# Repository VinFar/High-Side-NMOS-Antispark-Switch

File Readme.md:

High Side milliOhm NMOS Anti Spark Switch
===
# Introduction

This PCB is an Anti-Spark switch for high capacitive loads (100A, 60V) and was especially designed for electric longboards.
It uses 10 TPW1R306PL milliOhm N-MOSFET, which have a Rdson of around 90 uOhm in the worst case,
which theoretically enables a maximum current of around 125A with sufficient cooling.

Inspired by the [DieBieMS](https://github.com/DieBieEngineering/DieBieMS) it uses a BQ76200PWR HighSide MOSFET driver,
to enable the high switching with NMOS.

## Features

The PCB includes the following features:
  - dimensions: 74mm x 38.2mm
  - maximum current of at least 125A (more with additional copper and cooling)
  - maximum voltage of 60V
  - controlled dI/dt with capacitor and current limiting resistor
  - 10 TPW1R306PL N-channel MOSFET
  - BQ76200PWR High Side MOSFET Driver
  - A TPS7A4101DGNR 12V 50mA LDO
  - A holder for a LittleFuse BF1
  - 4 pin JST XH connector for external switch or MCU
  - exposed pcb traces to add solder or a copper bar for lower resistance

### Versions
  - V0.1 is the initial version (08.09.19)
  - V0.2 uses 10 TPW1R306PL mosfet instead of two IRFS7530 (09.09.19)

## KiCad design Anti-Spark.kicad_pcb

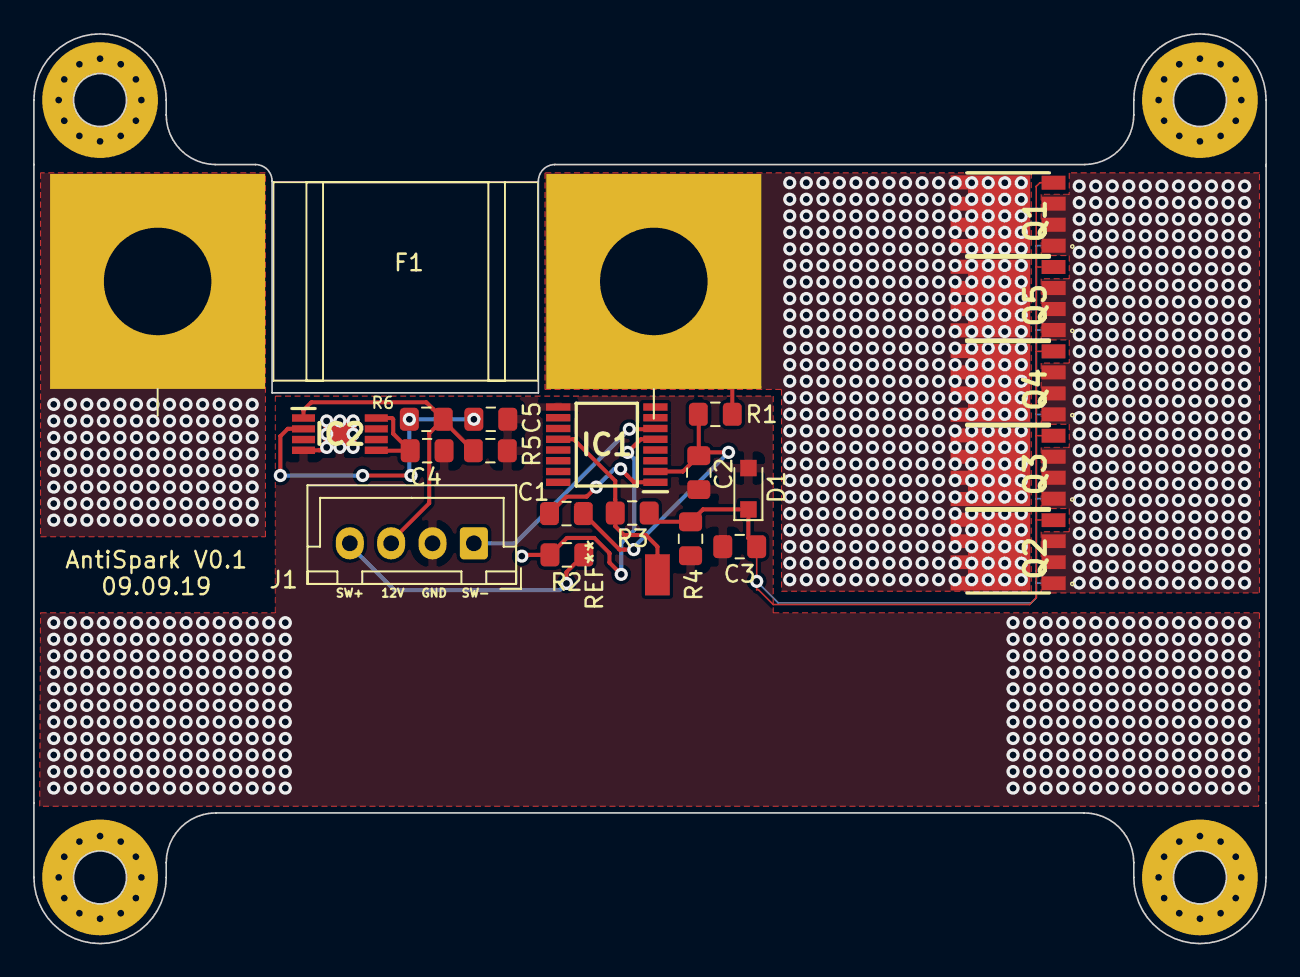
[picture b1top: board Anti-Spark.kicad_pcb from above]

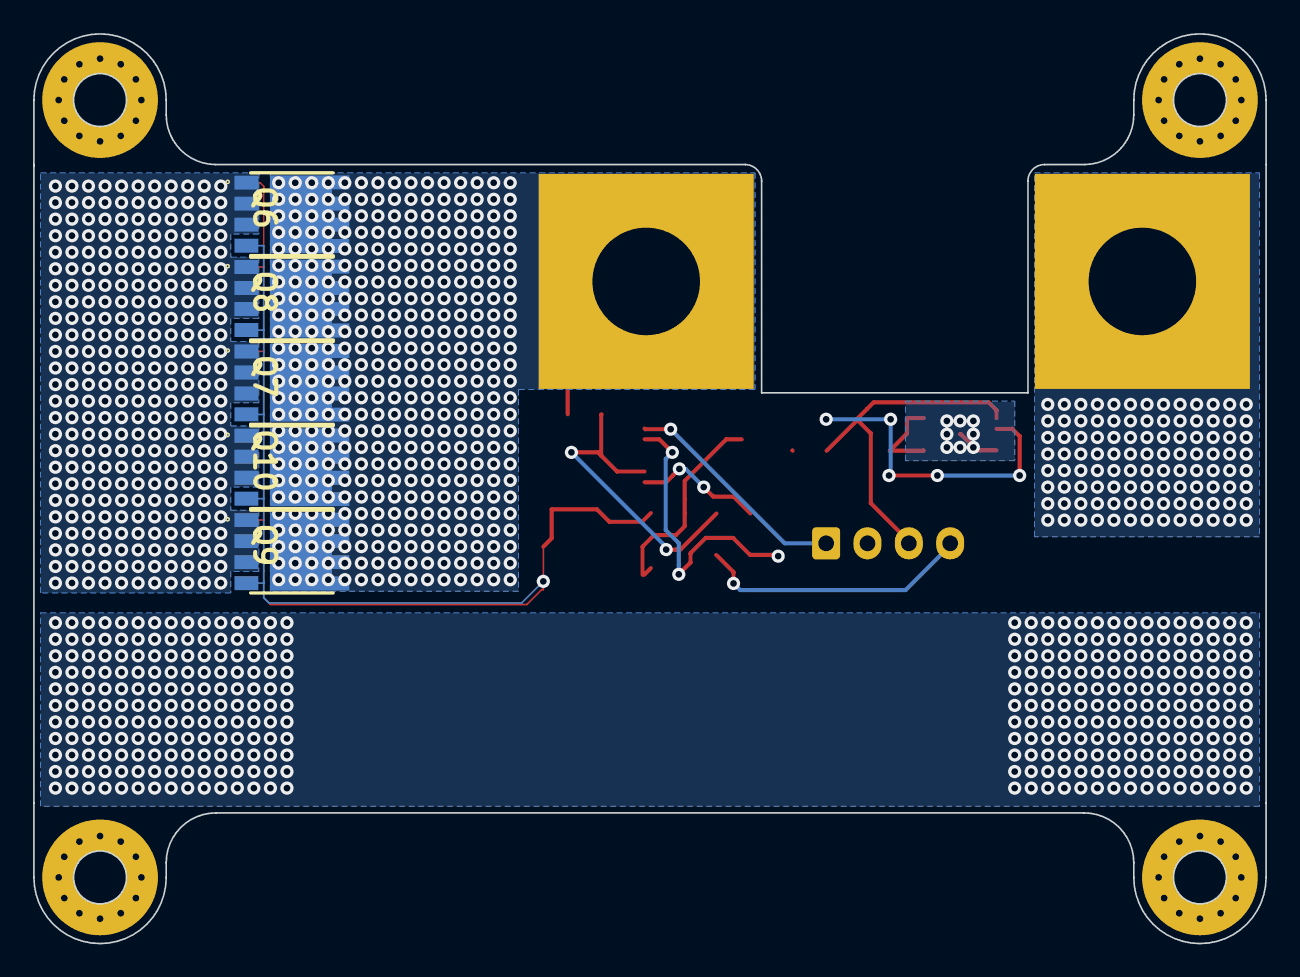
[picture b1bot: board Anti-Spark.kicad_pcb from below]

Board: 2 copper layers, 74.5 x 55.0 mm, 26 parts (5 on the bottom side), 13 nets.

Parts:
C1, C4, C5: 1uF; C_0805_2012Metric_Pad1.15x1.40mm_HandSolder
C2, C3: 100nF; C_0805_2012Metric_Pad1.15x1.40mm_HandSolder
D1: 18V; D_SOD-323_HandSoldering
F1: Fuse; littleFuseBF1
IC1: BQ76200PWR; SOP65P640X120-16N
IC2: TPS7A4101DGNR; SOP65P490X110-9N
J1: Conn_01x04_Male; JST_XH_B4B-XH-A_1x04_P2.50mm_Vertical
Q1, Q2, Q3, Q4, Q5, Q6, Q7, Q8, Q9, Q10: TPW1R306PL,L1Q; SOP_ADVANCE
R1: 100; R_0805_2012Metric_Pad1.15x1.40mm_HandSolder
R2: 0; R_0805_2012Metric_Pad1.15x1.40mm_HandSolder
R3: 2M; R_0805_2012Metric_Pad1.15x1.40mm_HandSolder
R4: 10M; R_0805_2012Metric_Pad1.15x1.40mm_HandSolder
R5: 92.301k; R_0805_2012Metric_Pad1.15x1.40mm_HandSolder
R6: 10k; R_0805_2012Metric_Pad1.15x1.40mm_HandSolder

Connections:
-BATT: C2.2, C3.2, C4.2, C5.2, D1.2, IC1.9, IC2.4, IC2.9, J1.2, R4.2, R5.1
FUSE+: F1.1, Q1.5, Q1.6, Q1.7, Q1.8, Q1.9, Q2.5, Q2.6, Q2.7, Q2.8, Q2.9, Q3.5, Q3.6, Q3.7, Q3.8, Q3.9, Q4.5, Q4.6, Q4.7, Q4.8, Q4.9, Q5.5, Q5.6, Q5.7, Q5.8, Q5.9, Q6.5, Q6.6, Q6.7, Q6.8, Q6.9, Q7.5, Q7.6, Q7.7, Q7.8, Q7.9, Q8.5, Q8.6, Q8.7, Q8.8, Q8.9, Q9.5, Q9.6, Q9.7, Q9.8, Q9.9, Q10.5, Q10.6, Q10.7, Q10.8, Q10.9, R1.1
unnamed: C1.1, IC1.1
unnamed: C1.2, C2.1, IC1.2, R1.2
unnamed: C3.1, D1.1, Q1.4, Q2.4, Q3.4, Q4.4, Q5.4, Q6.4, Q7.4, Q8.4, Q9.4, Q10.4, R3.2, R4.1
unnamed: C4.1, IC2.5, IC2.8
unnamed: C5.1, IC2.1, J1.3, R6.2
unnamed: IC1.5, R2.2
unnamed: IC1.12, R3.1
unnamed: IC2.2, R5.2, R6.1
SW+: J1.4, R2.1
SW-: IC1.6, J1.1
VESC: Q1.1, Q1.2, Q1.3, Q2.1, Q2.2, Q2.3, Q3.1, Q3.2, Q3.3, Q4.1, Q4.2, Q4.3, Q5.1, Q5.2, Q5.3, Q6.1, Q6.2, Q6.3, Q7.1, Q7.2, Q7.3, Q8.1, Q8.2, Q8.3, Q9.1, Q9.2, Q9.3, Q10.1, Q10.2, Q10.3

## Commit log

2019-09-08 add: pictures
2019-09-08 ch: pictures
2019-09-08 add: gnd plane for logic
2019-09-08 add: first version of Readme
2019-09-08 add: autosave from KiCad
2019-09-08 ch: image of pcb
2019-09-08 ch: readme
2019-09-08 ch: max current
2019-09-08 ch: features, current
2019-09-09 ch: new version with 10 mosfets
2019-09-11 updated PCB to V0.1
2019-09-11 add: step of pcb, copper and heatsink
2021-11-22 updated schematic to V0.2 Board file is corrupted
